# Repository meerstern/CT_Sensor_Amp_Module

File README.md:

# CTセンサアンプ基板  
CT Sensor Amp Module

## 概要 
  * 本基板はクランプ式CTセンサの出力を増幅してRMS値(実効値)に変換する基板です  
  * 交流電流に応じたRMS値(実効値)をアナログ値(直流)として得ることができます  
  * シャント抵抗、RMS値の演算ICを搭載しているため、交流電流の実効値をアナログ値として得ることが可能です  
  * 実効値をアナログ値として得られるため、マイコン側での高サンプリングAD変換やRMS演算等が不要です  
  * CTセンサ入力アンプ[INA181A1アンプ][1]、RMS換算[LTC1966][2]、低オフセット出力アンプ[MCP6V62][3]を使用しています  
  * シャント抵抗は49.9Ω、10Ω、1Ω、0.3Ωの4種類から選択できます  
  * シャント抵抗、CTセンサによって異なりますが、最小0.1A~最大300A程度まで測定可能です(3.3V電源時)  
  * 基板サイズ25mm x30mm、固定穴M3x2 幅20mm
  
## 換算式
  INA181A1によるゲイン20倍、出力段アンプゲイン3倍で合計60倍の増幅率です  

  VOUT= (I x Gain x R)/CT  
  I = (VOUT x CT)/(Gain x R)  
  VOUT:アナログ出力電圧(V)、I:CTセンサ対象電流(A)、Gain:60倍(固定)、R:シャント抵抗(Ω)、CT:巻き線比  
  
  例　VOUT=(IxGainxR)/(CT比)=(Ix60x49.9)/3000   

## シャント抵抗と測定電流範囲目安
  * 1:3000のCTセンサを用いた場合の各シャント抵抗における最小電流と最大電流目安です    
  * 最大電流は増幅アンプ飽和の目安となる電圧から設定しています  
  * 最小電流はオフセット電圧が数10mV生じるため、影響を無視できる目安として設定しています  

| シャント抵抗 | 最小電流A(電源3.3V) | 最大電流A(電源3.3V) | 最小電流A(電源5V) | 最大電流A(電源5V) |
|:-----------|:------------|:------------|:------------|:------------|
| 49.9 | 0.1 | 3 | 0.1 | 5 |
| 10.0 | 0.5 | 15 |	0.5 |	23 |
| 1.0 |	5 | 150 | 5	| 230 |
| 0.3 |	10 | 340 | 10 | 500 |				
			 
## 注意 
  * CTセンサは同梱されていません  
  * 巻き線比1:2000~3000前後ののCTセンサを使用してください  
  * 使用時は必ずシャント抵抗のいずれか1つをジャンパさせてください  
  * CTセンサの特性上、活線で2次側を解放すると数kVの電圧が発生しCTの損傷や感電の恐れがあります  
  * CTの損傷や感電を防ぐため、出力保護素子を内蔵したCTセンサの使用を推奨します  
  * 電源は3.3V、5Vに対応していますが、5V電源の方がレンジを確保できるため、より多くの電流を測定できます  
  * 電源電圧以上の出力はアンプが飽和するため、正しく出力されません    
  * AD変換の入力インピーダンスやオフセット電圧等の影響で、電流0Aでも数10mV程度の出力電圧が生じます  
  * 各シャント抵抗における最小電流以下の小さな電流測定には向きません  
  * 50Hz/60Hzの商用電源の電流をCTセンサで測定する用途を想定しています  
  * RMS演算ICによって真の実効値演算を得ていますが、大きな歪みやノイズが多い場合、正しく測定できない場合があります  
  * 回路上のローパスフィルタで高周波をカットオフしているため、数百Hz以上の電流変化は測定できません  
  
 ## 販売サイト
  * [スイッチサイエンス][4]

[1]: https://www.tij.co.jp/product/jp/INA181 "*1"
[2]: https://www.analog.com/jp/products/ltc1966.html "*2"
[3]: https://www.microchip.com/en-us/product/MCP6V62 "*3"
[4]: https://www.switch-science.com/products/7559

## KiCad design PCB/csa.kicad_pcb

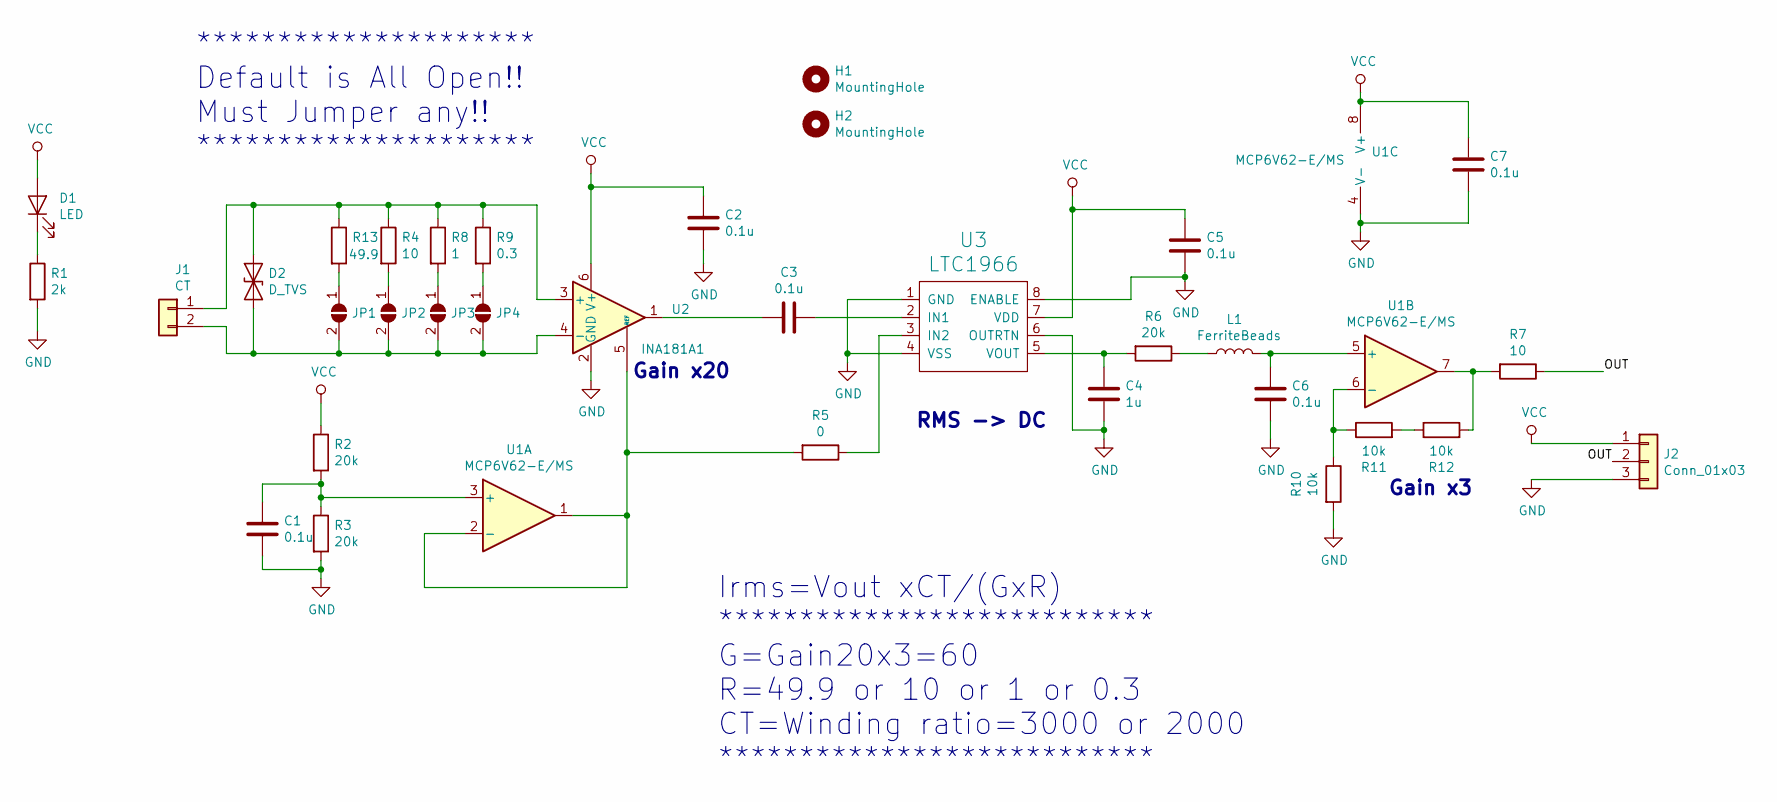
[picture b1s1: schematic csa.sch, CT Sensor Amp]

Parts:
C1, C2, C3, C5, C6, C7: 0.1u; C_0603_1608Metric
C4: 1u; C_0603_1608Metric
D1: LED; D_0603_1608Metric
D2: D_TVS; R_0603_1608Metric
H1, H2: MountingHole; MountingHole_3.2mm_M3
J1: CT; TerminalBlock_RND_205-00012_1x02_P5.00mm_Horizontal
J2: Conn_01x03; PinHeader_1x03_P2.54mm_Vertical
JP1, JP2, JP3, JP4: SolderJumper_2_Open; SolderJumper-2_P1.3mm_Open_TrianglePad1.0x1.5mm
L1: FerriteBeads; L_0603_1608Metric
R1: 2k; R_0603_1608Metric
R2, R3, R6: 20k; R_0603_1608Metric
R4: 10; R_1206_3216Metric
R5: 0; R_0603_1608Metric
R7: 10; R_0603_1608Metric
R8: 1; R_1206_3216Metric
R9: 0.3; R_1206_3216Metric
R10, R11, R12: 10k; R_0603_1608Metric
R13: 49.9; R_1206_3216Metric
U1: MCP6V62-E/MS; TSSOP-8_3x3mm_P0.65mm
U2: INA181A1; SOT-23-6
U3: LTC1966; TSSOP-8_3x3mm_P0.65mm

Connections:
/OUT: J2.2, R7.1
GND: C1.2, C2.2, C4.2, C5.2, C6.2, C7.2, J2.3, R1.2, R3.2, R10.2, U1.4 (V-), U2.2 (GND), U3.1 (GND), U3.4 (VSS), U3.6 (OUTRTN), U3.8 (ENABLE)
unnamed: C1.1, R2.2, R3.1, U1.3 (+)
unnamed: C3.1, U3.2 (IN1)
unnamed: C3.2, U2.1
unnamed: C4.1, R6.2, U3.5 (VOUT)
unnamed: C6.1, L1.2, U1.5 (+)
unnamed: D1.1 (K), R1.1
unnamed: D2.1 (A1), J1.1, R4.1, R8.1, R9.1, R13.1, U2.3 (+)
unnamed: D2.2 (A2), J1.2, JP1.2 (B), JP2.2 (B), JP3.2 (B), JP4.2 (B), U2.4 (-)
unnamed: JP1.1 (A), R13.2
unnamed: JP2.1 (A), R4.2
unnamed: JP3.1 (A), R8.2
unnamed: JP4.1 (A), R9.2
unnamed: L1.1, R6.1
unnamed: R5.1, U3.3 (IN2)
unnamed: R5.2, U1.1, U1.2 (-), U2.5 (REF)
unnamed: R10.1, R11.1, U1.6 (-)
unnamed: R11.2, R12.1
unnamed: R7.2, R12.2, U1.7
VCC: C2.1, C5.1, C7.1, D1.2 (A), J2.1, R2.1, U1.8 (V+), U2.6 (V+), U3.7 (VDD)

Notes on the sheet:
Gain x20
Gain x3
Irms=Vout xCT/(GxR) *************************** G=Gain20x3=60 R=49.9 or 10 or 1 or 0.3 CT=Winding ratio=3000 or 2000 ***************************
********************* Default is All Open!! Must Jumper any!! *********************
RMS -> DC

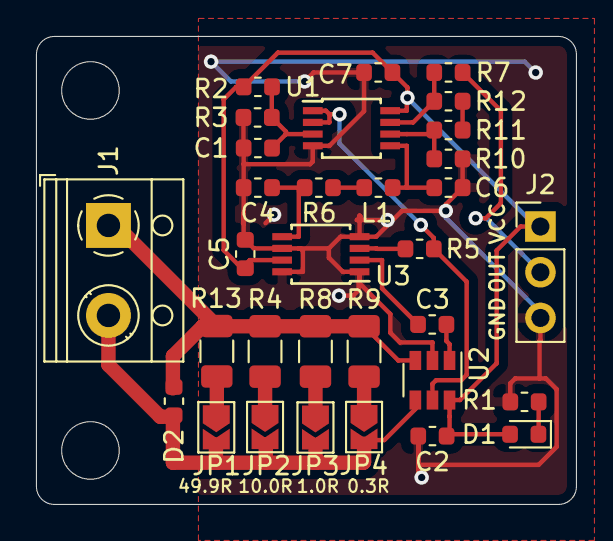
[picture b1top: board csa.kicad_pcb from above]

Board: 2 copper layers, 30.0 x 26.0 mm, 34 parts (0 on the bottom side), 21 nets.

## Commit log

2021-09-13 Add images
2021-09-13 Add pcb data
2022-12-06 Add shop link
